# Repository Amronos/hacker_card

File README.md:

# Hacker Card

This is an STM32 devboard which has an RGB LED that you can switch between by pressing a button.

Slack username: @amronos

## BOM

| Part Name | Quantity |
| --- | --- |
| CL10A106KP8NNNC | 1 |
| STM32C011F6P6 | 1 |
| CL05B104KO5NNNC | 3 |
| RGB LED | 1 |
| 220 ohm Resistor | 6 |
| Push Button | 2 |

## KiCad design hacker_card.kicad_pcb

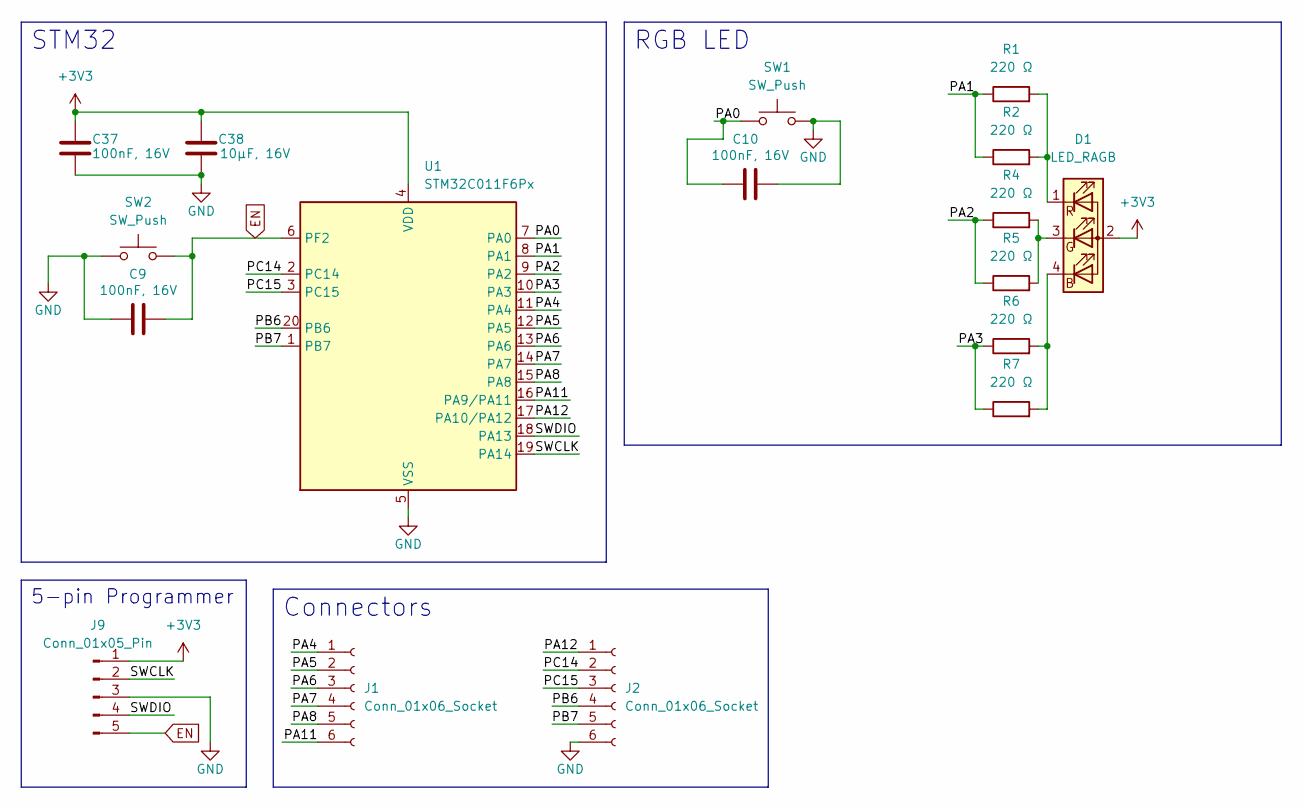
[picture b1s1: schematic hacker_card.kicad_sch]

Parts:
C9, C10, C37: 100nF, 16V; C_0402_1005Metric; MPN CL05B104KO5NNNC
C38: 10µF, 16V; C_0603_1608Metric; MPN GRT188R61C106KE13D
D1: LED_RAGB; LED_D5.0mm-4_RGB; MPN TJ-L5FYTXHMCYLCRGB-A5; JLCPCB Part # C331057
J1, J2: Conn_01x06_Socket; PinSocket_1x06_P2.54mm_Vertical
J9: Conn_01x05_Pin; PinHeader_1x05_P2.54mm_Vertical
R1, R2, R4, R5, R6, R7: 220 Ω; R_Axial_DIN0516_L15.5mm_D5.0mm_P20.32mm_Horizontal
SW1, SW2: SW_Push; SW_Push_1P1T_NO_CK_KMR2; MPN KMR223G LFG
U1: STM32C011F6Px; TSSOP-20_4.4x6.5mm_P0.65mm

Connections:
+3V3: C37.1, C38.1, D1.2 (A), J9.1, U1.4 (VDD)
/PA0: C10.1, SW1.1, U1.7 (PA0)
/PA1: R1.1, R2.1, U1.8 (PA1)
/PA2: R4.1, R5.1, U1.9 (PA2)
/PA3: R6.1, R7.1, U1.10 (PA3)
/PA4: J1.1, U1.11 (PA4)
/PA5: J1.2, U1.12 (PA5)
/PA6: J1.3, U1.13 (PA6)
/PA7: J1.4, U1.14 (PA7)
/PA8: J1.5, U1.15 (PA8)
/PA11: J1.6, U1.16 (PA9/PA11)
/PA12: J2.1, U1.17 (PA10/PA12)
/PB6: J2.4, U1.20 (PB6)
/PB7: J2.5, U1.1 (PB7)
/PC14: J2.2, U1.2 (PC14)
/PC15: J2.3, U1.3 (PC15)
/SWCLK: J9.2, U1.19 (PA14)
/SWDIO: J9.4, U1.18 (PA13)
EN: C9.2, J9.5, SW2.2, U1.6 (PF2)
GND: C9.1, C10.2, C37.2, C38.2, J2.6, J9.3, SW1.2, SW2.1, U1.5 (VSS)
unnamed: D1.4 (BK), R6.2, R7.2
unnamed: D1.3 (GK), R4.2, R5.2
unnamed: D1.1 (RK), R1.2, R2.2

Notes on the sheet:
5-pin Programmer
Connectors
STM32
RGB LED

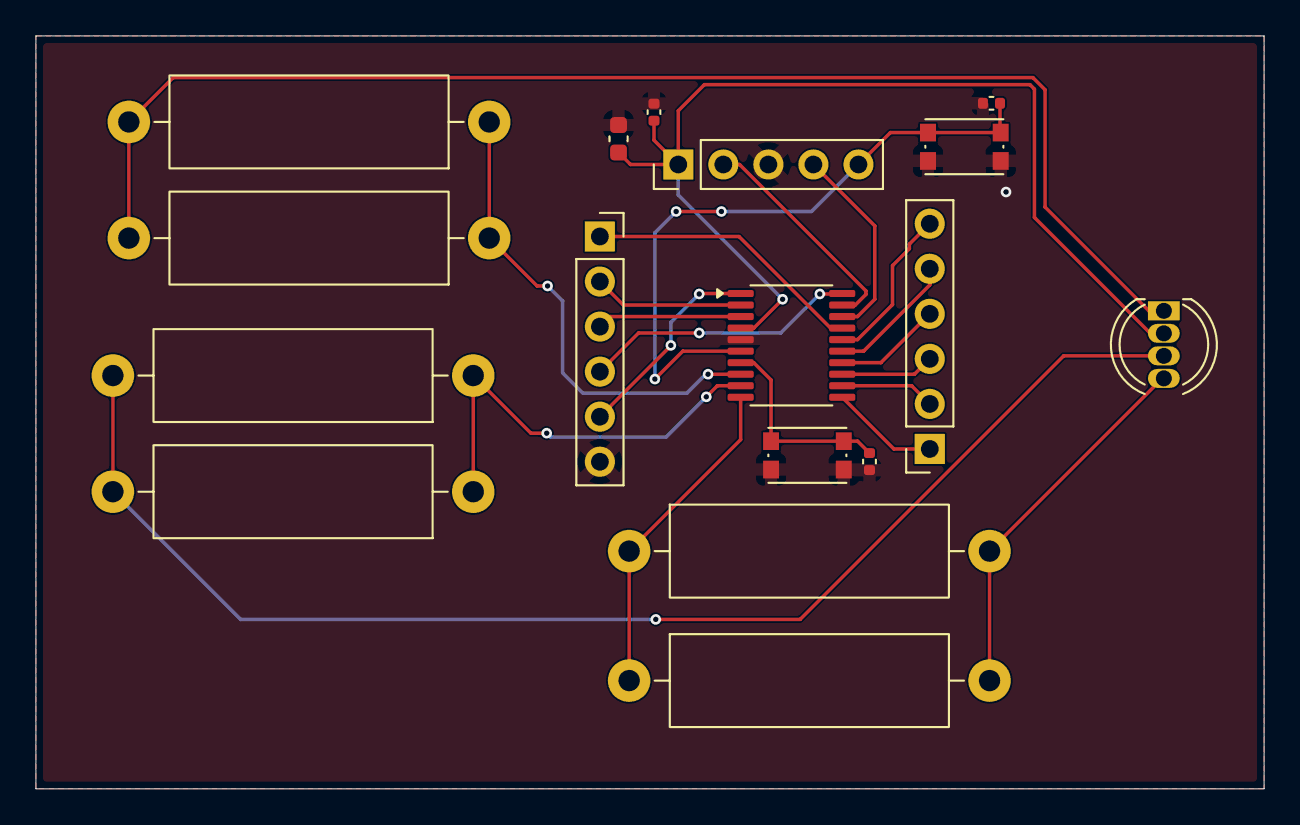
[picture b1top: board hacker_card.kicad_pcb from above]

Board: 2 copper layers, 69.2 x 42.5 mm, 17 parts (0 on the bottom side), 23 nets.
